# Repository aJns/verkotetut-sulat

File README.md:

# verkotetut-sulat
ELT-23100 Verkotetut sulautetut järjestelmät kurssin harkkatyö

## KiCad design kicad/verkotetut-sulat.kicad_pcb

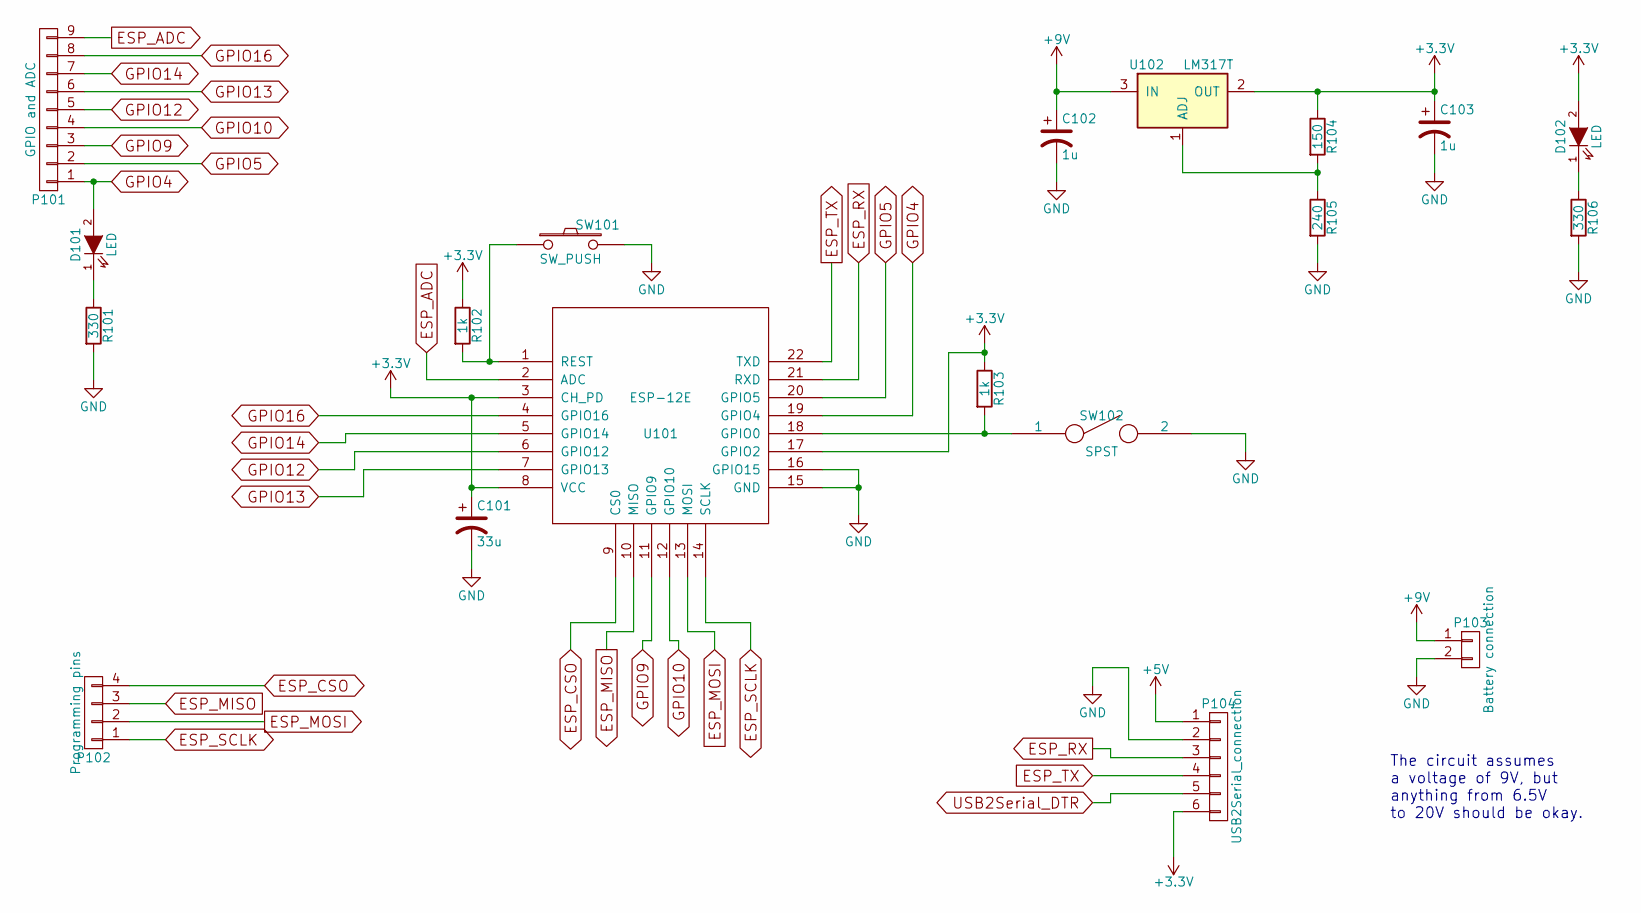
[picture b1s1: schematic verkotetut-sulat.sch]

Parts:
C101: 33u; C_Radial_D10_L21_P5
C102, C103: 1u; C_Radial_D5_L11_P2
D101, D102: LED; LED_0603
P101: GPIO and ADC; Pin_Header_Straight_1x09
P102: Programming pins; Pin_Header_Straight_1x04
P103: Battery connection; Pin_Header_Straight_1x02
P104: USB2Serial_connection; Pin_Header_Straight_1x06
R101, R106: 330; R_0603
R102, R103: 1k; R_0603
R104: 150; R_0805
R105: 240; R_0805
SW101: SW_PUSH; SW_SPST_B3S-1000
SW102: SPST; SPDT_SMD_SIDE
U101: ESP-12E
U102: LM317T; TO-220_Neutral123_Horizontal

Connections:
+3V3: C101.1, C103.1, D102.2 (A), P104.6, R102.1, R103.1, R104.1, U101.3 (CH_PD), U101.8 (VCC), U101.17 (GPIO2), U102.2 (OUT)
+5V: P104.1
+9V: C102.1, P103.1, U102.3 (IN)
ESP_ADC: P101.9, U101.2 (ADC)
ESP_CSO: P102.4, U101.9 (CS0)
ESP_MISO: P102.3, U101.10 (MISO)
ESP_MOSI: P102.2, U101.13 (MOSI)
ESP_RX: P104.3, U101.21 (RXD)
ESP_SCLK: P102.1, U101.14 (SCLK)
ESP_TX: P104.4, U101.22 (TXD)
GND: C101.2, C102.2, C103.2, P103.2, P104.2, R101.2, R105.2, R106.2, SW101.2, SW102.2, U101.15 (GND), U101.16 (GPIO15)
GPIO4: D101.2 (A), P101.1, U101.19 (GPIO4)
GPIO5: P101.2, U101.20 (GPIO5)
GPIO9: P101.3, U101.11 (GPIO9)
GPIO10: P101.4, U101.12 (GPIO10)
GPIO12: P101.5, U101.6 (GPIO12)
GPIO13: P101.6, U101.7 (GPIO13)
GPIO14: P101.7, U101.5 (GPIO14)
GPIO16: P101.8, U101.4 (GPIO16)
unnamed: D101.1 (K), R101.1
unnamed: D102.1 (K), R106.1
unnamed: R102.2, SW101.1, U101.1 (REST)
unnamed: R103.2, SW102.1, U101.18 (GPIO0)
unnamed: R104.2, R105.1, U102.1 (ADJ)
USB2Serial_DTR: P104.5

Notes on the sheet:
The circuit assumes a voltage of 9V, but anything from 6.5V to 20V should be okay.

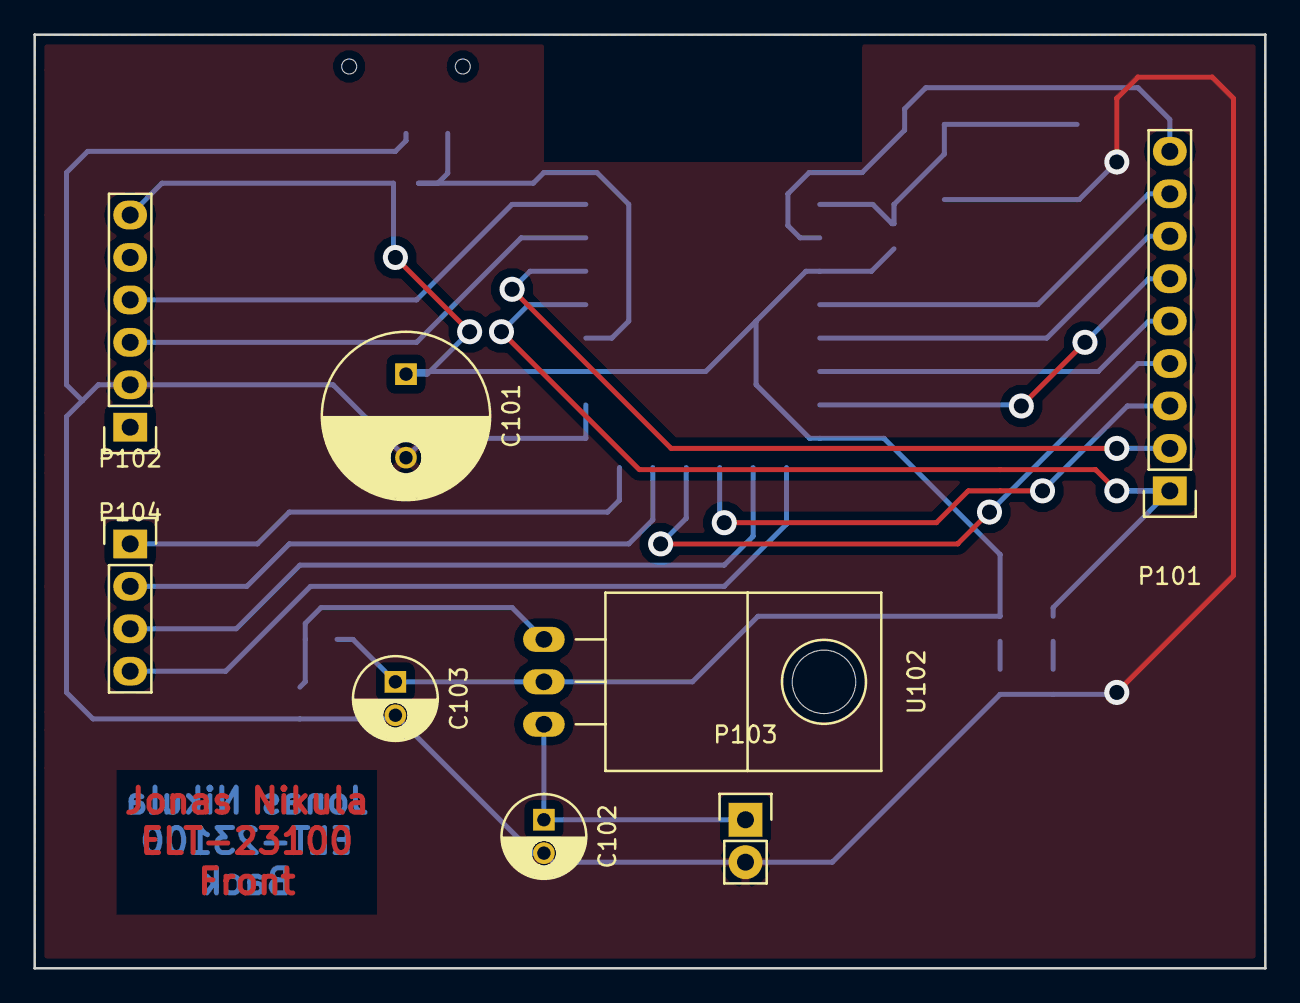
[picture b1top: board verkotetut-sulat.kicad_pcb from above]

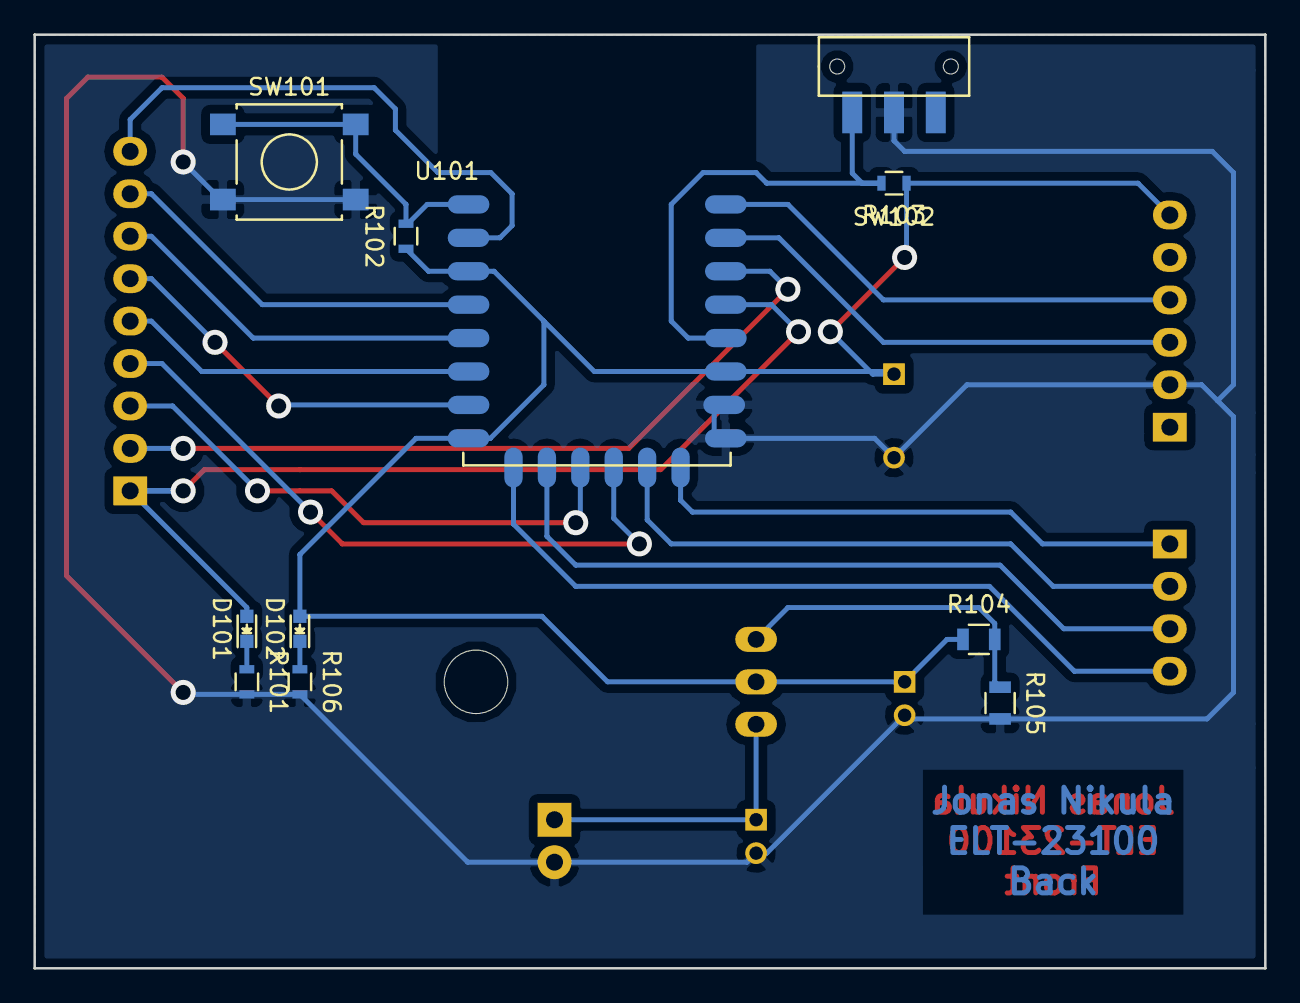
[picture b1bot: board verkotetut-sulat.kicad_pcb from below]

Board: 2 copper layers, 73.7 x 55.9 mm, 19 parts (11 on the bottom side), 23 nets.

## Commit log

2016-11-15 Make the initial connections in the schematic
2016-11-15 Add ESP non-OS SDK
2016-11-15 Finish schematic
2016-11-15 Add a LED to GPIO4 and a pinout for ADC
2016-11-15 Create netlist
2016-11-16 Start PCB design
2016-11-16 Work on pcb
2016-11-23 Draw all connections
2016-11-24 Pour copper
2016-11-24 Increase via size
2016-11-24 Add text to board
2016-11-24 Export masks
2016-12-07 Add example blink code
2016-12-07 Connect to wifi
2016-12-08 Make contact with laptop using hostname
2016-12-08 Receive data from server
2016-12-08 Get valid message from server
2016-12-08 Do some cleanup
2016-12-08 Read led_state from website
2016-12-08 Light led according to web site state
2016-12-09 Add web component
2016-12-11 Make a simple web thingy
2016-12-11 Tweaks to make everything work together
2016-12-12 Add POST to change led_state on button press
2016-12-12 Setup latex
2016-12-12 Move all actual content to a separate file
2016-12-23 Start writing the design section
2016-12-23 Use biblatex
2016-12-23 Write about the hardware
2016-12-23 Add pictures of the finished PCB
2016-12-24 Write about the software
2016-12-26 Write some more about the software
2016-12-26 Write more about ESP programming
2016-12-27 Write about the peculiarities of ESP programming
2016-12-27 Start writing the summary
2016-12-28 Write the summary
